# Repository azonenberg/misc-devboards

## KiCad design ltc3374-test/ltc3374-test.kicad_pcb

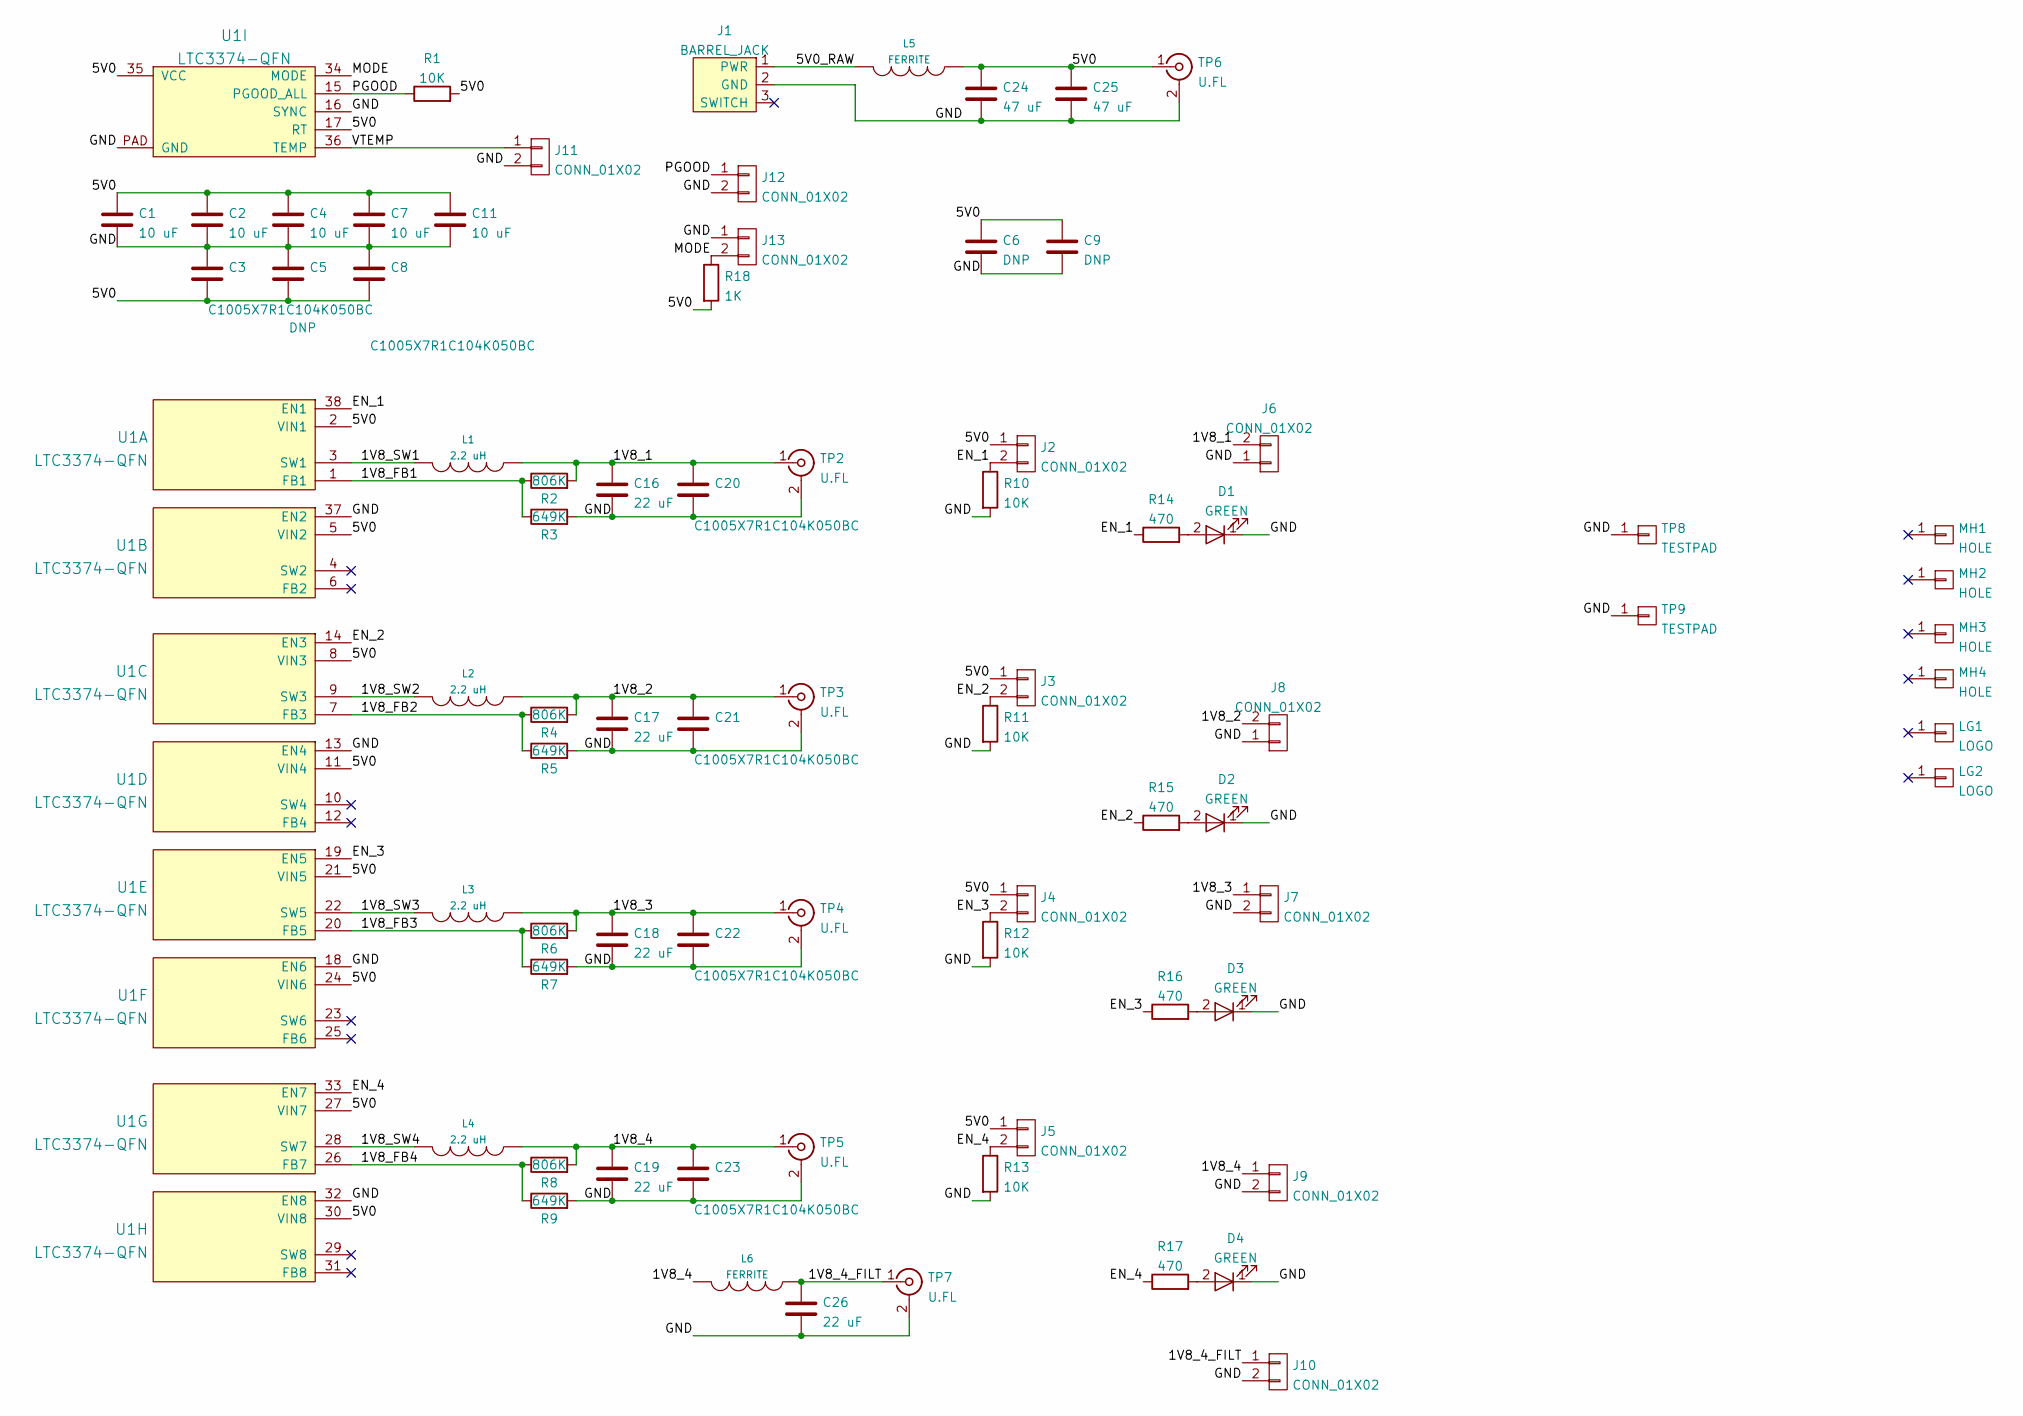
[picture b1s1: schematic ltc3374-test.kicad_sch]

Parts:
C1, C2, C4, C7, C11: 10 uF; EIA_0805_CAP_NOSILK
C3, C8, C20, C21, C22, C23: C1005X7R1C104K050BC; EIA_0402_CAP_NOSILK
C5: DNP; EIA_0402_CAP_NOSILK
C6, C9: DNP; EIA_1210_CAP_NOSILK
C16, C17, C18, C19, C26: 22 uF; EIA_1206_CAP_NOSILK
C24, C25: 47 uF; EIA_1210_CAP_NOSILK
D1, D2, D3, D4: GREEN; EIA_0603_CAP_NOSILK
J1: BARREL_JACK; CONN_CUI_PJ-058BH_HIPWR_BARREL_NOSLOT
J2, J3, J4, J5, J11, J12, J13: CONN_01X02; CONN_HEADER_2.54MM_1x2
J6, J7, J8, J9, J10: CONN_01X02; TERMBLOCK_PHOENIX_COMBICON_3.5MM_2POS_1984617
L1, L2, L3, L4: 2.2 uH; INDUCTOR_YUDEN_NRS5030
L5, L6: FERRITE; EIA_0603_INDUCTOR_NOSILK
LG1: LOGO; LONGTHING-1200DPI
LG2: LOGO; Logo_silk_polarity_center_5x1.4mm
MH1, MH2, MH3, MH4: HOLE; MECHANICAL_CLEARANCEHOLE_4_40
R1: 10K; EIA_0402_RES_NOSILK
R2, R4, R6, R8: 806K; EIA_0402_RES_NOSILK
R3, R5, R7, R9: 649K; EIA_0402_RES_NOSILK
R10, R11, R12, R13: 10K; EIA_0402_RES_NOSILK_FLIPCHIP
R14, R15, R16, R17: 470; EIA_0402_RES_NOSILK_FLIPCHIP
R18: 1K; EIA_0402_RES_NOSILK
TP2, TP3, TP4, TP5, TP6, TP7: U.FL; CONN_U.FL_TE_1909763-1
TP8, TP9: TESTPAD; TESTPOINT_SMT_KEYSTONE_5016
U1: LTC3374-QFN; QFN_38_0.5MM_5x7MM

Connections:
/1V8_1: C16.1, C20.1, J6.2, L1.1, R2.2, TP2.1 (In)
/1V8_2: C17.1, C21.1, J8.2, L2.1, R4.2, TP3.1 (In)
/1V8_3: C18.1, C22.1, J7.1, L3.1, R6.2, TP4.1 (In)
/1V8_4: C19.1, C23.1, J9.1, L4.1, L6.2, R8.2, TP5.1 (In)
/1V8_4_FILT: C26.1, J10.1, L6.1, TP7.1 (In)
/1V8_FB1: R2.1, R3.1, U1.1 (FB1)
/1V8_FB2: R4.1, R5.1, U1.7 (FB3)
/1V8_FB3: R6.1, R7.1, U1.20 (FB5)
/1V8_FB4: R8.1, R9.1, U1.26 (FB7)
/1V8_SW1: L1.2, U1.3 (SW1)
/1V8_SW2: L2.2, U1.9 (SW3)
/1V8_SW3: L3.2, U1.22 (SW5)
/1V8_SW4: L4.2, U1.28 (SW7)
/5V0: C1.1, C2.1, C3.2, C4.1, C5.2, C6.1, C7.1, C8.2, C9.1, C11.1, C24.1, C25.1, J2.1, J3.1, J4.1, J5.1, L5.1, R1.2, R18.2, TP6.1 (In), U1.2 (VIN1), U1.5 (VIN2), U1.8 (VIN3), U1.11 (VIN4), U1.17 (RT), U1.21 (VIN5), U1.24 (VIN6), U1.27 (VIN7), U1.30 (VIN8), U1.35 (VCC)
/5V0_RAW: J1.1 (PWR), L5.2
/EN_1: J2.2, R10.1, R14.1, U1.38 (EN1)
/EN_2: J3.2, R11.1, R15.1, U1.14 (EN3)
/EN_3: J4.2, R12.1, R16.1, U1.19 (EN5)
/EN_4: J5.2, R13.1, R17.1, U1.33 (EN7)
/GND: C1.2, C2.2, C3.1, C4.2, C5.1, C6.2, C7.2, C8.1, C9.2, C11.2, C16.2, C17.2, C18.2, C19.2, C20.2, C21.2, C22.2, C23.2, C24.2, C25.2, C26.2, D1.1 (K), D2.1 (K), D3.1 (K), D4.1 (K), J1.2 (GND), J6.1, J7.2, J8.1, J9.2, J10.2, J11.2, J12.2, J13.1, R3.2, R5.2, R7.2, R9.2, R10.2, R11.2, R12.2, R13.2, TP2.2 (Ext), TP3.2 (Ext), TP4.2 (Ext), TP5.2 (Ext), TP6.2 (Ext), TP7.2 (Ext), TP8.1, TP9.1, U1.13 (EN4), U1.16 (SYNC), U1.18 (EN6), U1.32 (EN8), U1.37 (EN2), U1.PAD (GND)
/MODE: J13.2, R18.1, U1.34 (MODE)
/PGOOD: J12.1, R1.1, U1.15 (PGOOD_ALL)
/VTEMP: J11.1, U1.36 (TEMP)
unnamed: D1.2 (A), R14.2
unnamed: D2.2 (A), R15.2
unnamed: D3.2 (A), R16.2
unnamed: D4.2 (A), R17.2

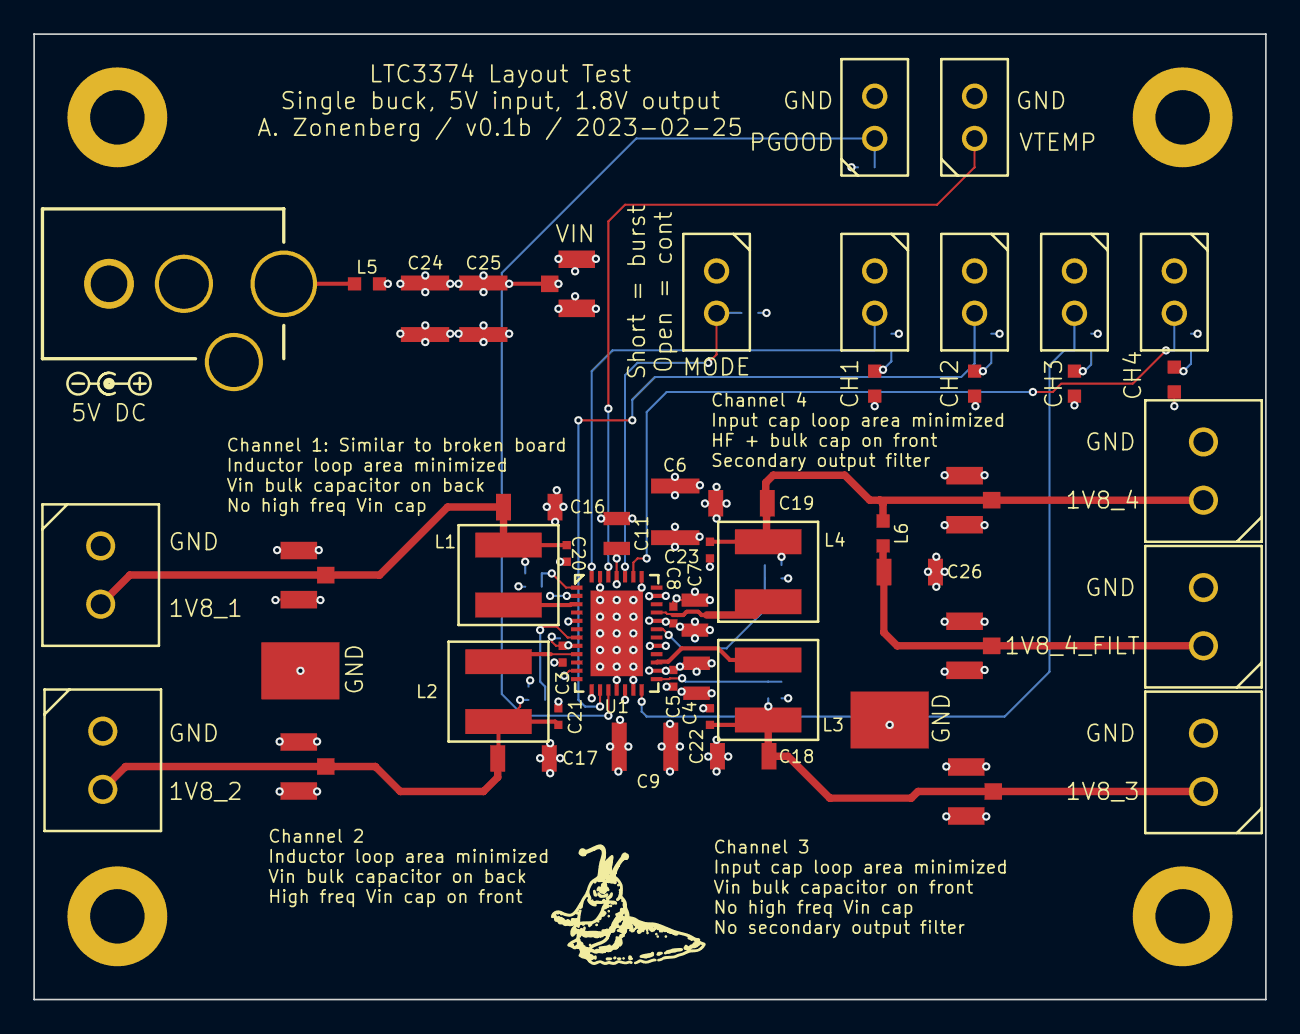
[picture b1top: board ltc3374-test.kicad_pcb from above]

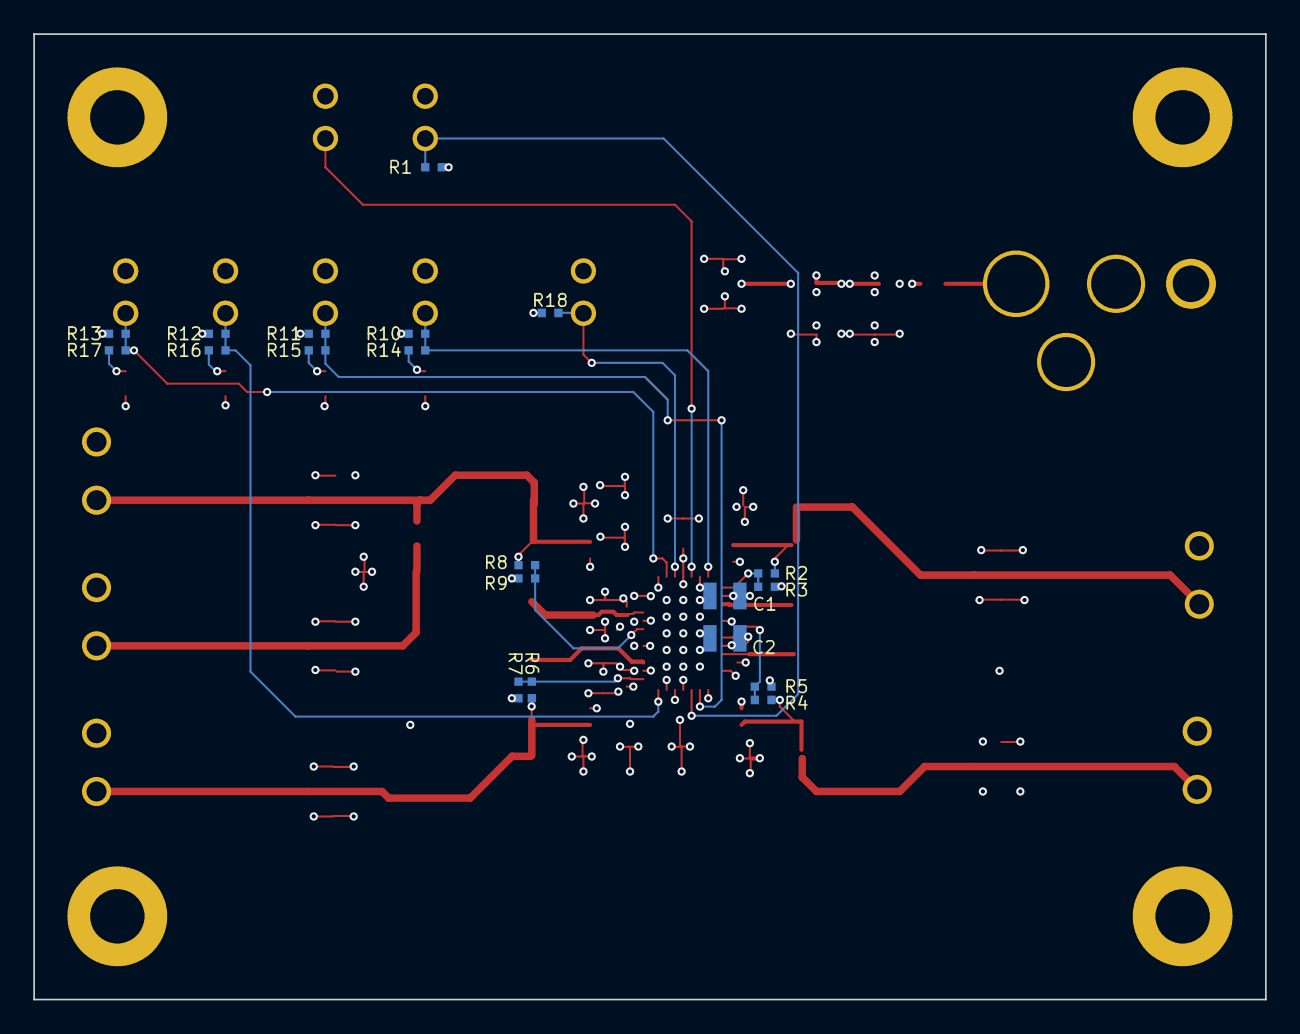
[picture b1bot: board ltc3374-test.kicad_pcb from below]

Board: 4 copper layers, 74.0 x 58.0 mm, 77 parts (20 on the bottom side), 27 nets.

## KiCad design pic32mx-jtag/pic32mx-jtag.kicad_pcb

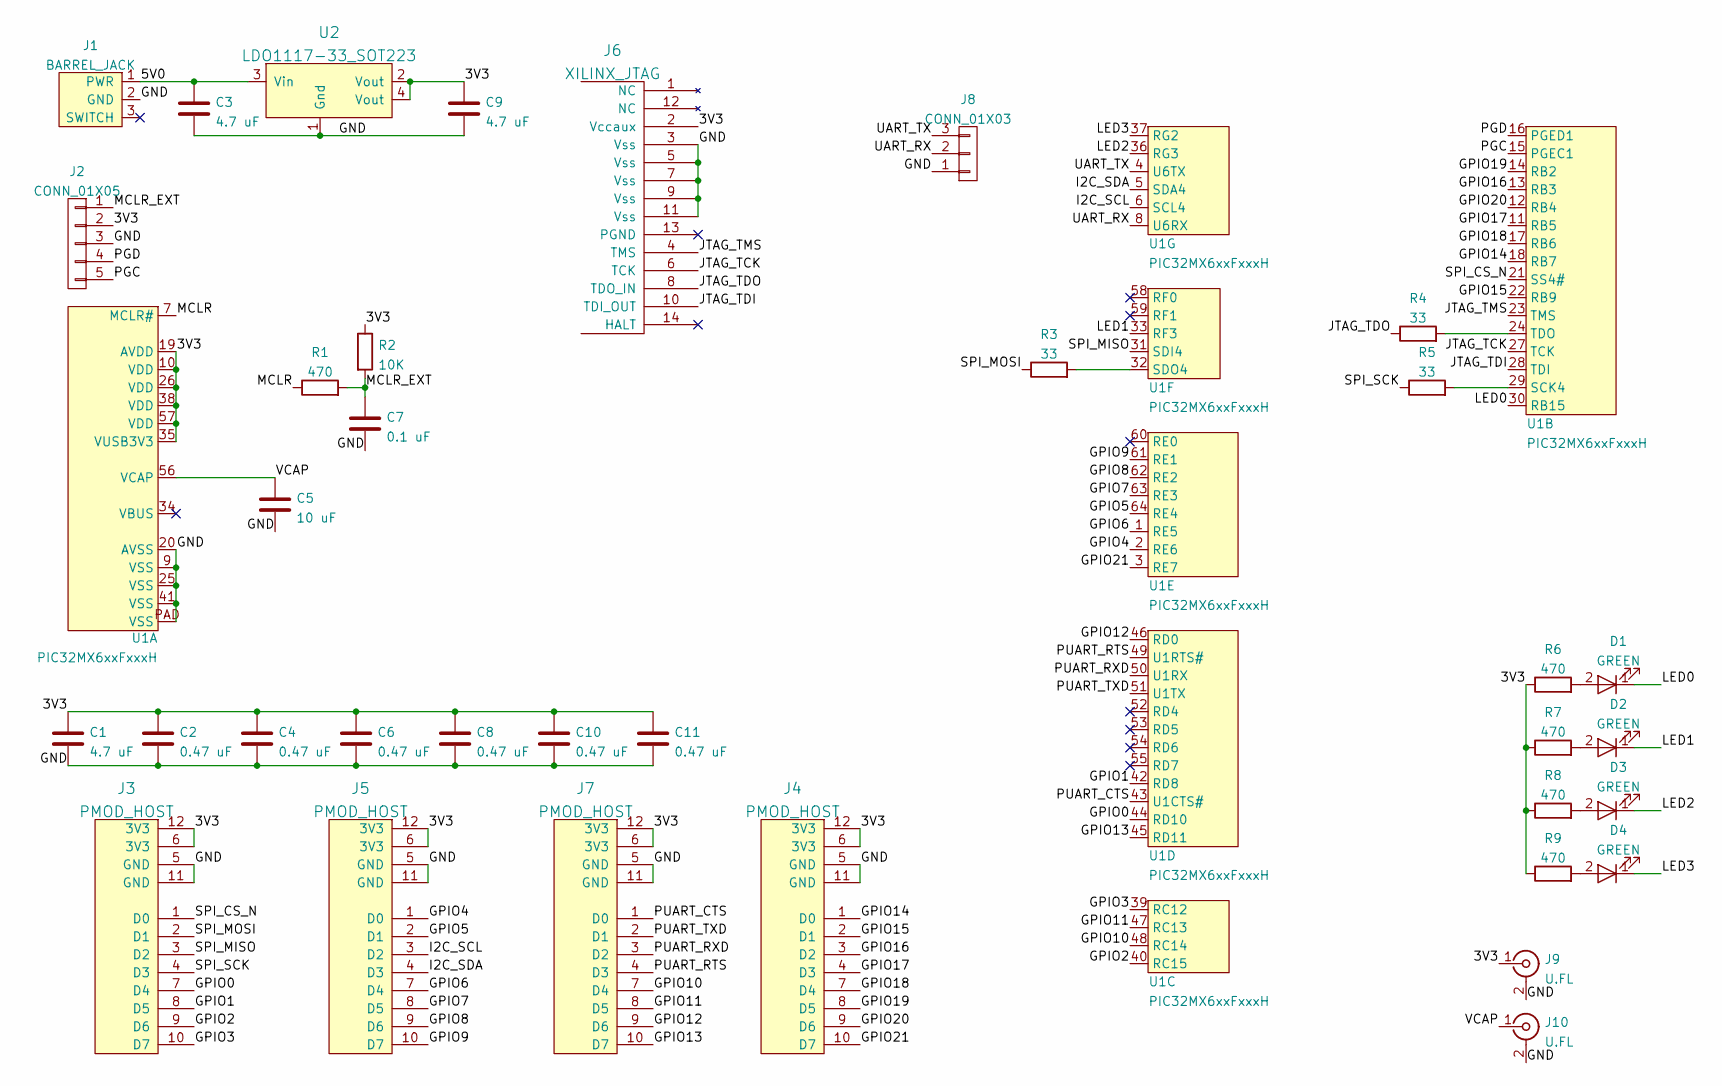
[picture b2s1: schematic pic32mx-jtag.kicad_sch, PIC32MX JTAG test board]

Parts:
C1, C3, C9: 4.7 uF; EIA_0603_CAP_NOSILK
C2, C4, C6, C8, C10, C11: 0.47 uF; EIA_0402_CAP_NOSILK
C5: 10 uF; EIA_0805_CAP_NOSILK
C7: 0.1 uF; EIA_0402_CAP_NOSILK
D1, D2, D3, D4: GREEN; EIA_0805_LED
J1: BARREL_JACK; CONN_CUI_PJ-058BH_HIPWR_BARREL_NOSLOT
J2: CONN_01X05; CONN_HEADER_2.54MM_1x5
J3, J4, J5, J7: PMOD_HOST; CONN_HEADER_2.54MM_2x6_RA_PMOD_HOST
J6: XILINX_JTAG; XILINX_JTAG_PTH_MOLEX_0878311420
J8: CONN_01X03; CONN_HEADER_2.54MM_1x3
J9, J10: U.FL; CONN_U.FL_TE_1909763-1
R1, R6, R7, R8, R9: 470; EIA_0402_RES_NOSILK
R2: 10K; EIA_0402_RES_NOSILK
R3, R4, R5: 33; EIA_0402_RES_NOSILK
U1: PIC32MX6xxFxxxH; QFP_64_0.5MM
U2: LDO1117-33_SOT223; SOT223-4

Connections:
/3V3: C1.1, C2.1, C4.1, C6.1, C8.1, C9.1, C10.1, C11.1, J2.2, J3.6 (3V3), J3.12 (3V3), J4.6 (3V3), J4.12 (3V3), J5.6 (3V3), J5.12 (3V3), J6.2 (Vccaux), J7.6 (3V3), J7.12 (3V3), J9.1 (In), R2.1, R6.1, R7.1, R8.1, R9.1, U1.10 (VDD), U1.19 (AVDD), U1.26 (VDD), U1.35 (VUSB3V3), U1.38 (VDD), U1.57 (VDD), U2.2 (Vout), U2.4 (Vout)
/5V0: C3.1, J1.1 (PWR), U2.3 (Vin)
/GND: C1.2, C2.2, C3.2, C4.2, C5.2, C6.2, C7.2, C8.2, C9.2, C10.2, C11.2, J1.2 (GND), J2.3, J3.5 (GND), J3.11 (GND), J4.5 (GND), J4.11 (GND), J5.5 (GND), J5.11 (GND), J6.3 (Vss), J6.5 (Vss), J6.7 (Vss), J6.9 (Vss), J6.11 (Vss), J7.5 (GND), J7.11 (GND), J8.1, J9.2 (Ext), J10.2 (Ext), U1.9 (VSS), U1.20 (AVSS), U1.25 (VSS), U1.41 (VSS), U1.PAD (VSS), U2.1 (Gnd)
/GPIO0: J3.7 (D4), U1.44 (RD10)
/GPIO1: J3.8 (D5), U1.42 (RD8)
/GPIO2: J3.9 (D6), U1.40 (RC15)
/GPIO3: J3.10 (D7), U1.39 (RC12)
/GPIO4: J5.1 (D0), U1.2 (RE6)
/GPIO5: J5.2 (D1), U1.64 (RE4)
/GPIO6: J5.7 (D4), U1.1 (RE5)
/GPIO7: J5.8 (D5), U1.63 (RE3)
/GPIO8: J5.9 (D6), U1.62 (RE2)
/GPIO9: J5.10 (D7), U1.61 (RE1)
/GPIO10: J7.7 (D4), U1.48 (RC14)
/GPIO11: J7.8 (D5), U1.47 (RC13)
/GPIO12: J7.9 (D6), U1.46 (RD0)
/GPIO13: J7.10 (D7), U1.45 (RD11)
/GPIO14: J4.1 (D0), U1.18 (RB7)
/GPIO15: J4.2 (D1), U1.22 (RB9)
/GPIO16: J4.3 (D2), U1.13 (RB3)
/GPIO17: J4.4 (D3), U1.11 (RB5)
/GPIO18: J4.7 (D4), U1.17 (RB6)
/GPIO19: J4.8 (D5), U1.14 (RB2)
/GPIO20: J4.9 (D6), U1.12 (RB4)
/GPIO21: J4.10 (D7), U1.3 (RE7)
/I2C_SCL: J5.3 (D2), U1.6 (SCL4)
/I2C_SDA: J5.4 (D3), U1.5 (SDA4)
/JTAG_TCK: J6.6 (TCK), U1.27 (TCK)
/JTAG_TDI: J6.10 (TDI_OUT), U1.28 (TDI)
/JTAG_TDO: J6.8 (TDO_IN), R4.1
/JTAG_TMS: J6.4 (TMS), U1.23 (TMS)
/LED0: D1.1 (K), U1.30 (RB15)
/LED1: D2.1 (K), U1.33 (RF3)
/LED2: D3.1 (K), U1.36 (RG3)
/LED3: D4.1 (K), U1.37 (RG2)
/MCLR: R1.1, U1.7 (MCLR#)
/MCLR_EXT: C7.1, J2.1, R1.2, R2.2
/PGC: J2.5, U1.15 (PGEC1)
/PGD: J2.4, U1.16 (PGED1)
/PUART_CTS: J7.1 (D0), U1.43 (U1CTS#)
/PUART_RTS: J7.4 (D3), U1.49 (U1RTS#)
/PUART_RXD: J7.3 (D2), U1.50 (U1RX)
/PUART_TXD: J7.2 (D1), U1.51 (U1TX)
/SPI_CS_N: J3.1 (D0), U1.21 (SS4#)
/SPI_MISO: J3.3 (D2), U1.31 (SDI4)
/SPI_MOSI: J3.2 (D1), R3.1
/SPI_SCK: J3.4 (D3), R5.1
/UART_RX: J8.2, U1.8 (U6RX)
/UART_TX: J8.3, U1.4 (U6TX)
/VCAP: C5.1, J10.1 (In), U1.56 (VCAP)
unnamed: D1.2 (A), R6.2
unnamed: D2.2 (A), R7.2
unnamed: D3.2 (A), R8.2
unnamed: D4.2 (A), R9.2
unnamed: R3.2, U1.32 (SDO4)
unnamed: R4.2, U1.24 (TDO)
unnamed: R5.2, U1.29 (SCK4)

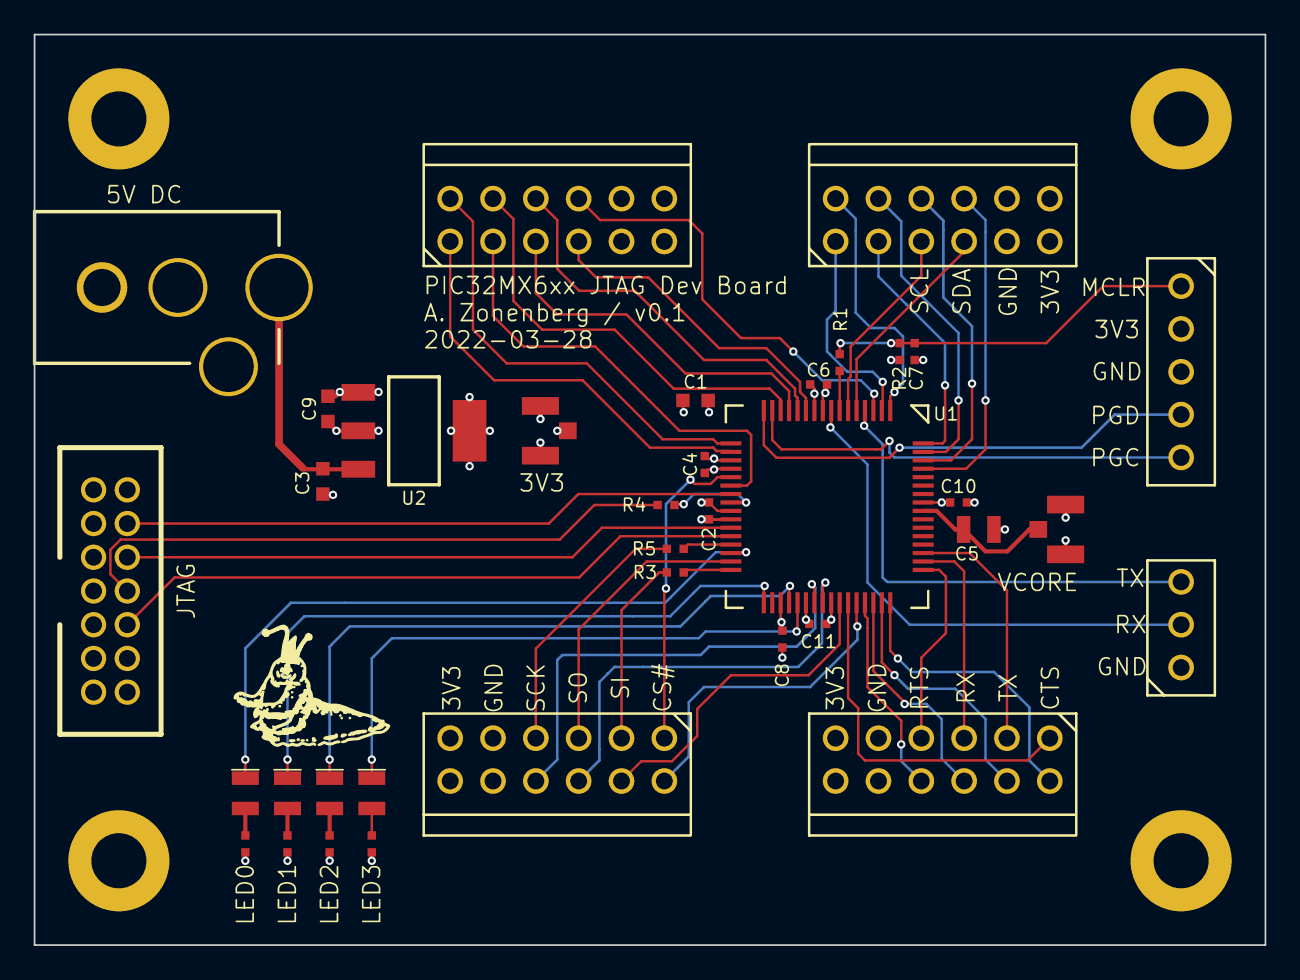
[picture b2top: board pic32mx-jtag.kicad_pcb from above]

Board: 4 copper layers, 73.0 x 54.0 mm, 36 parts (0 on the bottom side), 57 nets.

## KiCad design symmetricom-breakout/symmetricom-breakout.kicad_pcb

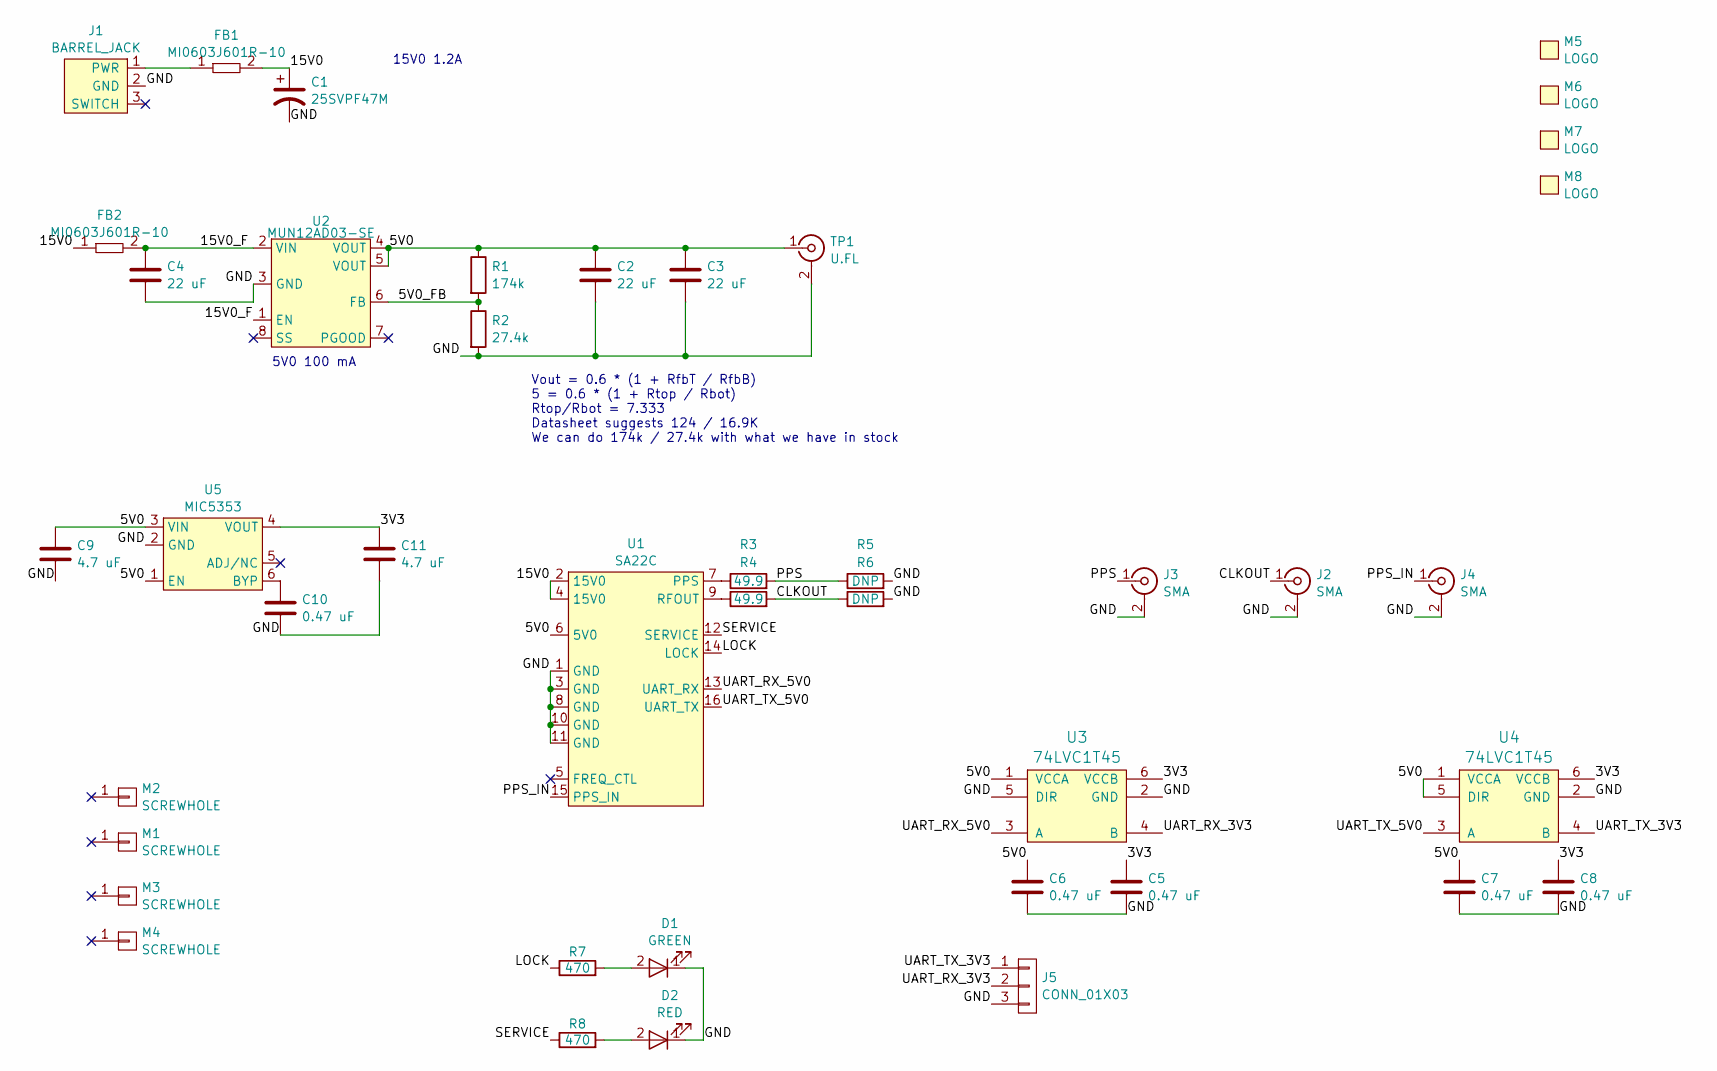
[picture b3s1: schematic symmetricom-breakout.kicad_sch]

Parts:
C1: 25SVPF47M; CAP_AL_6.3MM_SMT
C2, C3: 22 uF; EIA_1210_CAP_NOSILK
C4: 22 uF; EIA_1812_CAP_NOSILK
C5, C6, C7, C8, C10: 0.47 uF; EIA_0402_CAP_NOSILK
C9, C11: 4.7 uF; EIA_0603_CAP_NOSILK
D1: GREEN; EIA_0603_LED
D2: RED; EIA_0603_LED
FB1, FB2: MI0603J601R-10; EIA_0603_INDUCTOR_NOSILK
J1: BARREL_JACK; CONN_CUI_PJ-058BH_HIPWR_BARREL_NOSLOT
J2, J3, J4: SMA; CONN_SMA_EDGE_SAMTEC_SMA_J_P_H_ST_EM1
J5: CONN_01X03; CONN_HEADER_2.54MM_1x3
M1, M2, M3, M4: SCREWHOLE; MECHANICAL_CLEARANCEHOLE_M3
M5: LOGO; LONGTHING-1200DPI
M6: LOGO; Logo_silk_OSHW_6x6mm
M7: LOGO; Logo_silk_WEEE_3.4x5mm
M8: LOGO; Logo_silk_polarity_center_5x1.4mm
R1: 174k; EIA_0402_RES_NOSILK
R2: 27.4k; EIA_0402_RES_NOSILK
R3, R4: 49.9; EIA_0402_RES_NOSILK
R5, R6: DNP; EIA_0402_RES_NOSILK
R7, R8: 470; EIA_0402_RES_NOSILK
TP1: U.FL; CONN_U.FL_TE_1909763-1
U1: SA22C; CONN_HEADER_2MM_2x9_SMT
U2: MUN12AD03-SE; MODULE_CYNTEC_MUN12AD03-SE
U3, U4: 74LVC1T45; DFN_6_0.5MM_1.6x1.6MM_TI_DPK
U5: MIC5353; DFN_6_0.5MM_1.6x1.6MM_TI_DPK

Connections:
/3V3: C5.1, C8.1, C11.1, U3.6 (VCCB), U4.6 (VCCB), U5.4 (VOUT)
/5V0: C2.1, C3.1, C6.1, C7.1, C9.1, R1.1, TP1.1 (In), U1.6 (5V0), U2.4 (VOUT), U2.5 (VOUT), U3.1 (VCCA), U4.1 (VCCA), U4.5 (DIR), U5.1 (EN), U5.3 (VIN)
/5V0_FB: R1.2, R2.1, U2.6 (FB)
/15V0: C1.1, FB1.2, FB2.1, U1.2 (15V0), U1.4 (15V0)
/15V0_F: C4.1, FB2.2, U2.1 (EN), U2.2 (VIN)
/CLKOUT: J2.1 (In), R4.2, R6.1
/GND: C1.2, C2.2, C3.2, C4.2, C5.2, C6.2, C7.2, C8.2, C9.2, C10.2, C11.2, D1.1 (K), D2.1 (K), J1.2 (GND), J2.2 (Ext), J3.2 (Ext), J4.2 (Ext), J5.3, R2.2, R5.2, R6.2, TP1.2 (Ext), U1.1 (GND), U1.3 (GND), U1.8 (GND), U1.10 (GND), U1.11 (GND), U2.3 (GND), U3.2 (GND), U3.5 (DIR), U4.2 (GND), U5.2 (GND)
/LOCK: R7.1, U1.14 (LOCK)
/PPS: J3.1 (In), R3.2, R5.1
/PPS_IN: J4.1 (In), U1.15 (PPS_IN)
/SERVICE: R8.1, U1.12 (SERVICE)
/UART_RX_3V3: J5.2, U3.4 (B)
/UART_RX_5V0: U1.13 (UART_RX), U3.3 (A)
/UART_TX_3V3: J5.1, U4.4 (B)
/UART_TX_5V0: U1.16 (UART_TX), U4.3 (A)
unnamed: D1.2 (A), R7.2
unnamed: D2.2 (A), R8.2
unnamed: FB1.1, J1.1 (PWR)
unnamed: R3.1, U1.7 (PPS)
unnamed: R4.1, U1.9 (RFOUT)
unnamed: C10.1, U5.6 (BYP)

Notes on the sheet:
15V0 1.2A
5V0 100 mA
Vout = 0.6 * (1 + RfbT / RfbB) 5 = 0.6 * (1 + Rtop / Rbot) Rtop/Rbot = 7.333 Datasheet suggests 124 / 16.9K We can do 174k / 27.4k with what we have in stock

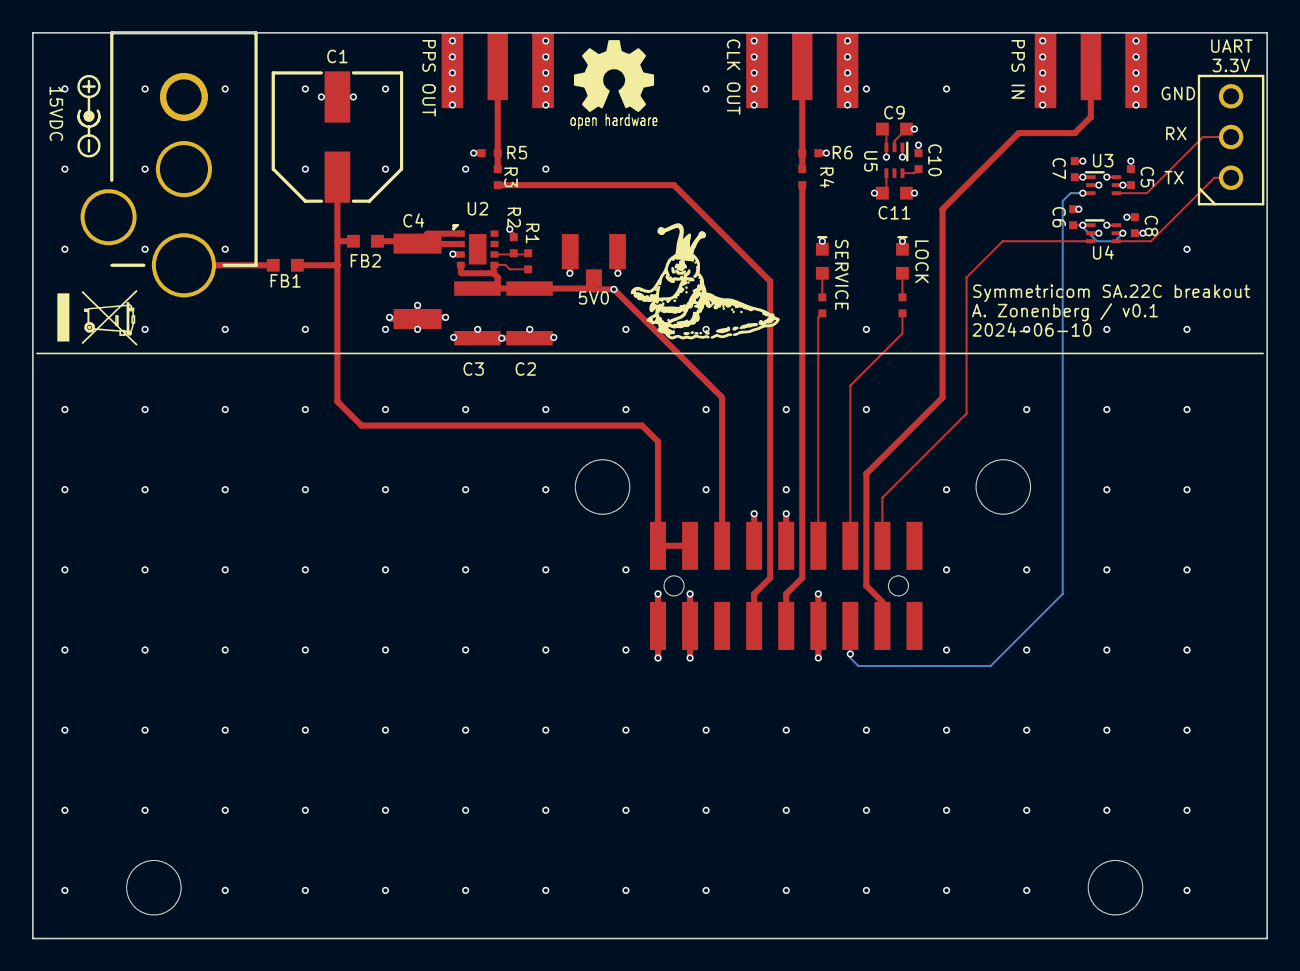
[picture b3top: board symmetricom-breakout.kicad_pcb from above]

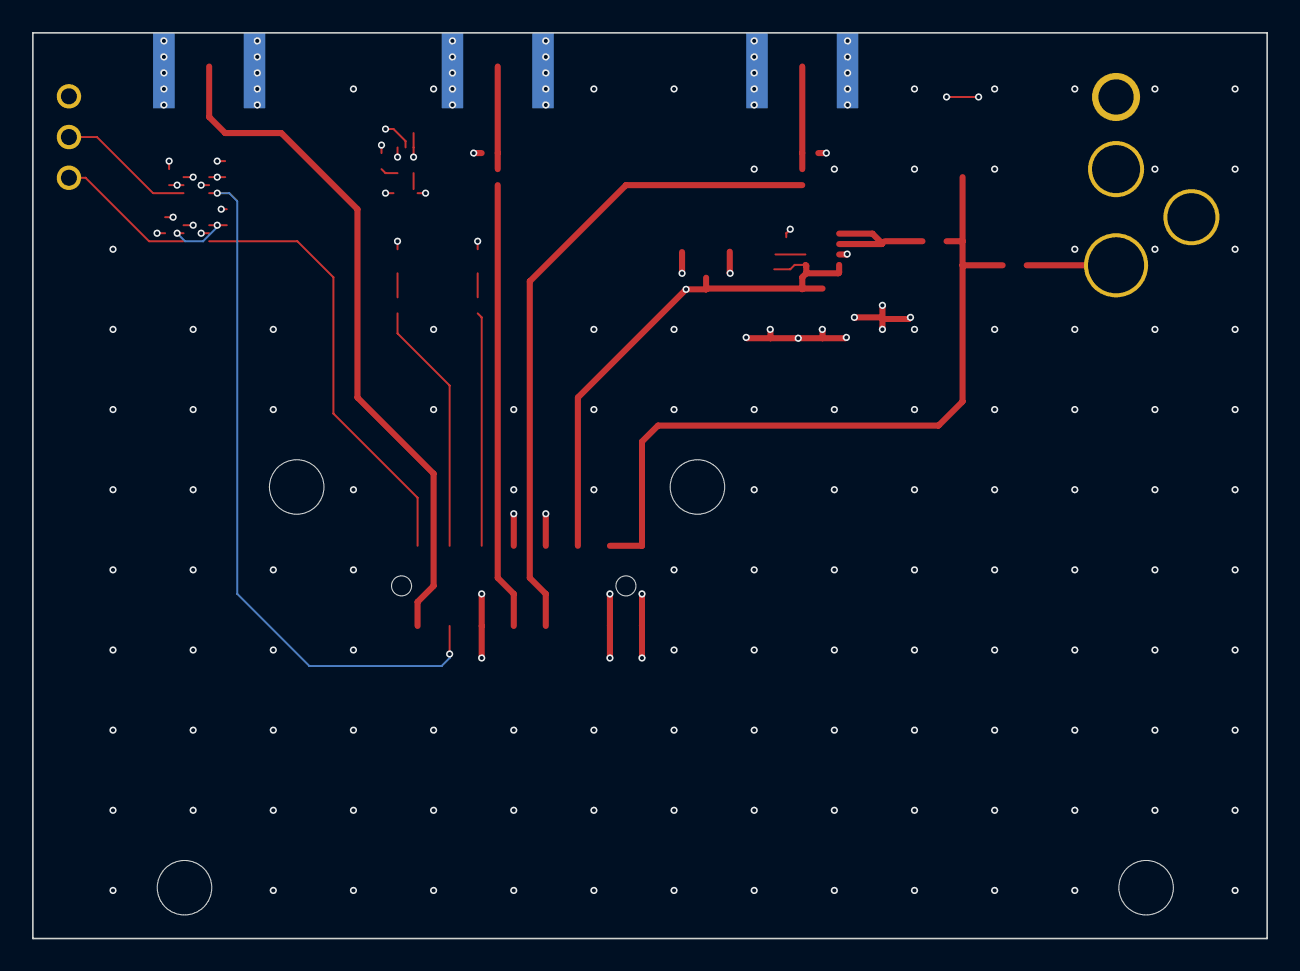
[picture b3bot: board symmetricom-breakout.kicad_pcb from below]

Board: 4 copper layers, 77.0 x 56.5 mm, 42 parts (4 on the bottom side), 21 nets.

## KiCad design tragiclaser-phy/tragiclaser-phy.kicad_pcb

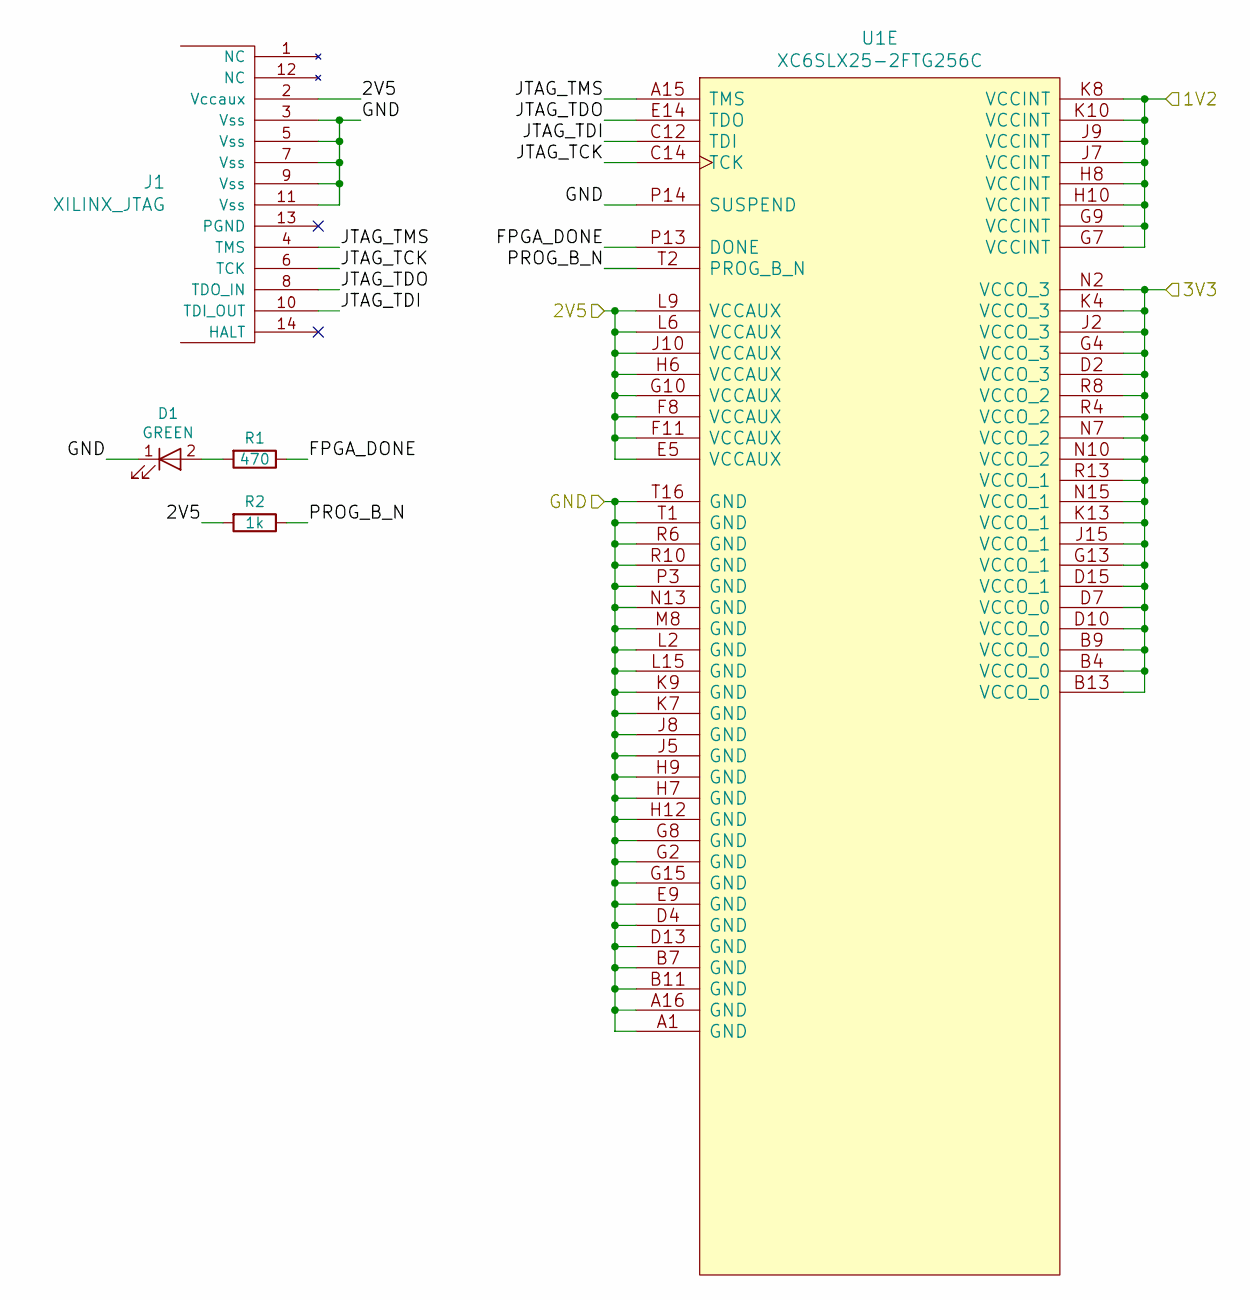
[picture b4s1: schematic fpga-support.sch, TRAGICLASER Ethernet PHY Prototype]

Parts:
D1: GREEN; EIA_0603_LED
J1: XILINX_JTAG; XILINX_JTAG_PTH_MOLEX_0878311420
R1: 470; EIA_0402_RES_NOSILK
R2: 1k; EIA_0402_RES_NOSILK
U1: XC6SLX25-2FTG256C; BGA_256_17x17_FULLARRAY_1MM

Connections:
/1V2: U1.G7 (VCCINT), U1.G9 (VCCINT), U1.H8 (VCCINT), U1.H10 (VCCINT), U1.J7 (VCCINT), U1.J9 (VCCINT), U1.K8 (VCCINT), U1.K10 (VCCINT); also elsewhere on the board
/2V5: J1.2 (Vccaux), R2.2, U1.E5 (VCCAUX), U1.F8 (VCCAUX), U1.F11 (VCCAUX), U1.G10 (VCCAUX), U1.H6 (VCCAUX), U1.J10 (VCCAUX), U1.L6 (VCCAUX), U1.L9 (VCCAUX); also elsewhere on the board
/3V3: U1.B4 (VCCO_0), U1.B9 (VCCO_0), U1.B13 (VCCO_0), U1.D2 (VCCO_3), U1.D7 (VCCO_0), U1.D10 (VCCO_0), U1.D15 (VCCO_1), U1.G4 (VCCO_3), U1.G13 (VCCO_1), U1.J2 (VCCO_3), U1.J15 (VCCO_1), U1.K4 (VCCO_3), U1.K13 (VCCO_1), U1.N2 (VCCO_3), U1.N7 (VCCO_2), U1.N10 (VCCO_2), U1.N15 (VCCO_1), U1.R4 (VCCO_2), U1.R8 (VCCO_2), U1.R13 (VCCO_1); also elsewhere on the board
/FPGA Support/FPGA_DONE: R1.1, U1.P13 (DONE)
/FPGA Support/JTAG_TCK: J1.6 (TCK), U1.C14 (TCK)
/FPGA Support/JTAG_TDI: J1.10 (TDI_OUT), U1.C12 (TDI)
/FPGA Support/JTAG_TDO: J1.8 (TDO_IN), U1.E14 (TDO)
/FPGA Support/JTAG_TMS: J1.4 (TMS), U1.A15 (TMS)
/FPGA Support/PROG_B_N: R2.1, U1.T2 (PROG_B_N)
/GND: D1.1 (K), J1.3 (Vss), J1.5 (Vss), J1.7 (Vss), J1.9 (Vss), J1.11 (Vss), U1.A1 (GND), U1.A16 (GND), U1.B7 (GND), U1.B11 (GND), U1.D4 (GND), U1.D13 (GND), U1.E9 (GND), U1.G2 (GND), U1.G8 (GND), U1.G15 (GND), U1.H7 (GND), U1.H9 (GND), U1.H12 (GND), U1.J5 (GND), U1.J8 (GND), U1.K7 (GND), U1.K9 (GND), U1.L2 (GND), U1.L15 (GND), U1.M8 (GND), U1.N13 (GND), U1.P3 (GND), U1.P14 (SUSPEND), U1.R6 (GND), U1.R10 (GND), U1.T1 (GND), U1.T16 (GND); also elsewhere on the board
unnamed: D1.2 (A), R1.2
